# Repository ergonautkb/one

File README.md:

# Ergonaut One

*Ergonaut One in Modern Case*

Ergonaut One is an open-source ergonomic wireless split mechanical keyboard designed by Ergonaut Keyboards.

Inspiration for the keyboard was taken from these projects:

* [Corne](https://github.com/foostan/crkbd) by [foostan](https://github.com/foostan)
* [Dao](https://github.com/yumagulovrn/dao-choc-ble) by [yumagulovrn](https://github.com/yumagulovrn)

## Idea

We wanted to create a pretty affordable, nice looking, and, most importantly, very DIY-friendly ergonomic wireless split keyboard with Gateron Low Profile switches.

## Photos

Gallery can be found on [imgur](https://imgur.com/a/sOBBtmQ).

## Features

* Low-profile, which will reduce strain on your beautiful hands;
* Split. You can put the keyboard where it'll be comfortable exactly for you;
* Pretty long battery life. 250mAh battery gives up to a month of usage without charging;
* Wide availability and range of [compatible keycaps](https://ergonautkb.com/docs/switches/gateron-low-profile#keycaps-compatibility);
* Easily replaceable [switches](https://ergonautkb.com/docs/switches/gateron-low-profile#ks-33-v2) thanks to hot-swap sockets;
* Budget-friendly, because:
  * It uses relatively cheap and widely available [Seeed Studio XIAO nRF52840](https://wiki.seeedstudio.com/XIAO_BLE/) as MCU;
  * It uses one PCB design for both halves of the keyboard;
  * Everything except PCB's, components and hardware (screws, nuts) can be 3D printed.
* Beginner-friendly, because:
  * PCB is easy to solder;
  * Cases are easy to print.
* Wireless by design - no unnecessary wires, no unused connectors on the board;
* Free in terms of hardware design. It's licensed under permissive [CERN-OHL-P v2](https://ohwr.org/cern_ohl_p_v2.pdf) license, which means:
  * you are free to manufacture it yourself;
  * you are free to sell your manufactured hardware for profit.

## Build Guide

BOM and Build Guide can be found in [Ergonaut Keyboards Documentation Portal](https://ergonautkb.com/docs/keyboards/ergonaut-one/intro).

## Firmware

Firmware can be found in [one-zmk-config](https://github.com/ergonautkb/one-zmk-config) repository.

## Gerbers

| Front                                            | Back                                                 |
| ------------------------------------------------ | ---------------------------------------------------- |
|  |  |

* [Gerbers for JLCPCB](../../releases/latest/download/pcb-JLCPCB_gerbers.zip)
* [Gerbers for PCBWay](../../releases/latest/download/pcb-PCBWay_gerbers.zip)

## Community projects

### Accessories

* [Frames for Magic Trackpad 2/3 and Laptops](https://www.thingiverse.com/thing:6447743) by [Alex Kh](https://www.thingiverse.com/alehano777/designs)

## Contacts

* Documentation portal: https://ergonautkb.com
* Telegram: https://ergonautkb.t.me
* Telegram (ru): https://ergonautkb_ru.t.me

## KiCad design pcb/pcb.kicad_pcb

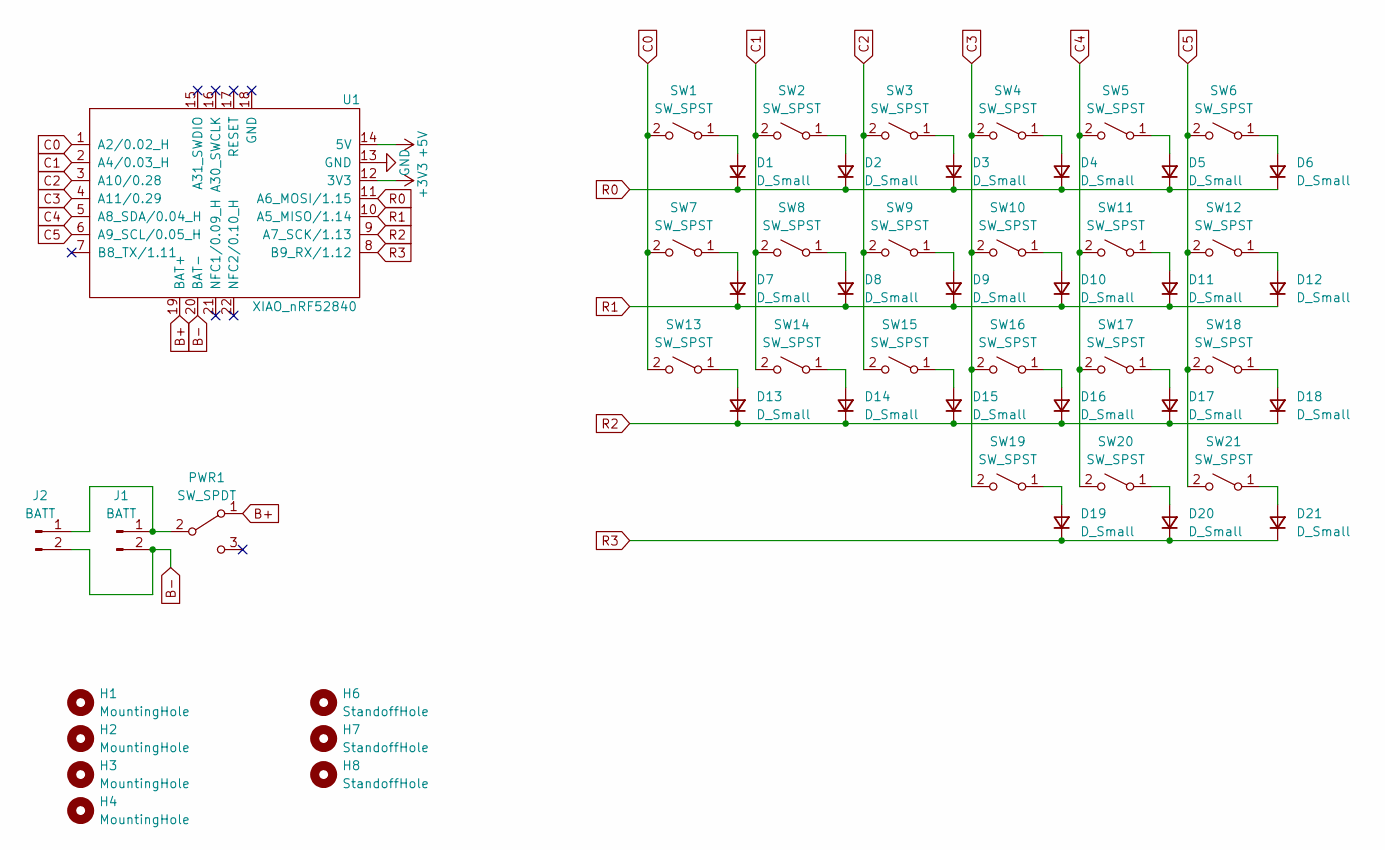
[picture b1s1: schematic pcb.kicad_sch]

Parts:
D1, D2, D3, D4, D5, D6, D7, D8, D9, D10, D11, D12, D13, D14, D15, D16, D17, D18, D19, D20, D21: D_Small; Diode_TH_SMD_DUAL
H1, H2, H3, H4: MountingHole; Hole_4.2mm
H6, H7, H8: StandoffHole; Hole_2.2mm
J1: BATT; Battery
J2: BATT; JST_SH_Battery_DUAL
PWR1: SW_SPDT; MSK-12C02_DUAL
SW1, SW2, SW3, SW4, SW5, SW6, SW7, SW8, SW9, SW10, SW11, SW12, SW13, SW14, SW15, SW16, SW17, SW18, SW19, SW20, SW21: SW_SPST; KS-27_KS-33_Hotswap_1U_DUAL
U1: XIAO_nRF52840; XIAO_nRF52840_DUAL

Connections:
+3V3: U1.12 (3V3)
+5V: U1.14 (5V)
B+: PWR1.1 (A), U1.19 (BAT+)
B-: J1.2, J2.2, U1.20 (BAT-)
C0: SW1.2 (B), SW7.2 (B), SW13.2 (B), U1.1 (A2/0.02_H)
C1: SW2.2 (B), SW8.2 (B), SW14.2 (B), U1.2 (A4/0.03_H)
C2: SW3.2 (B), SW9.2 (B), SW15.2 (B), U1.3 (A10/0.28)
C3: SW4.2 (B), SW10.2 (B), SW16.2 (B), SW19.2 (B), U1.4 (A11/0.29)
C4: SW5.2 (B), SW11.2 (B), SW17.2 (B), SW20.2 (B), U1.5 (A8_SDA/0.04_H)
C5: SW6.2 (B), SW12.2 (B), SW18.2 (B), SW21.2 (B), U1.6 (A9_SCL/0.05_H)
GND: U1.13 (GND)
unnamed: D1.2 (A), SW1.1 (A)
unnamed: D2.2 (A), SW2.1 (A)
unnamed: D3.2 (A), SW3.1 (A)
unnamed: D4.2 (A), SW4.1 (A)
unnamed: D5.2 (A), SW5.1 (A)
unnamed: D6.2 (A), SW6.1 (A)
unnamed: D7.2 (A), SW7.1 (A)
unnamed: D8.2 (A), SW8.1 (A)
unnamed: D9.2 (A), SW9.1 (A)
unnamed: D10.2 (A), SW10.1 (A)
unnamed: D11.2 (A), SW11.1 (A)
unnamed: D12.2 (A), SW12.1 (A)
unnamed: D13.2 (A), SW13.1 (A)
unnamed: D14.2 (A), SW14.1 (A)
unnamed: D15.2 (A), SW15.1 (A)
unnamed: D16.2 (A), SW16.1 (A)
unnamed: D17.2 (A), SW17.1 (A)
unnamed: D18.2 (A), SW18.1 (A)
unnamed: D19.2 (A), SW19.1 (A)
unnamed: D20.2 (A), SW20.1 (A)
unnamed: D21.2 (A), SW21.1 (A)
unnamed: J1.1, J2.1, PWR1.2 (B)
R0: D1.1 (K), D2.1 (K), D3.1 (K), D4.1 (K), D5.1 (K), D6.1 (K), U1.11 (A6_MOSI/1.15)
R1: D7.1 (K), D8.1 (K), D9.1 (K), D10.1 (K), D11.1 (K), D12.1 (K), U1.10 (A5_MISO/1.14)
R2: D13.1 (K), D14.1 (K), D15.1 (K), D16.1 (K), D17.1 (K), D18.1 (K), U1.9 (A7_SCK/1.13)
R3: D19.1 (K), D20.1 (K), D21.1 (K), U1.8 (B9_RX/1.12)

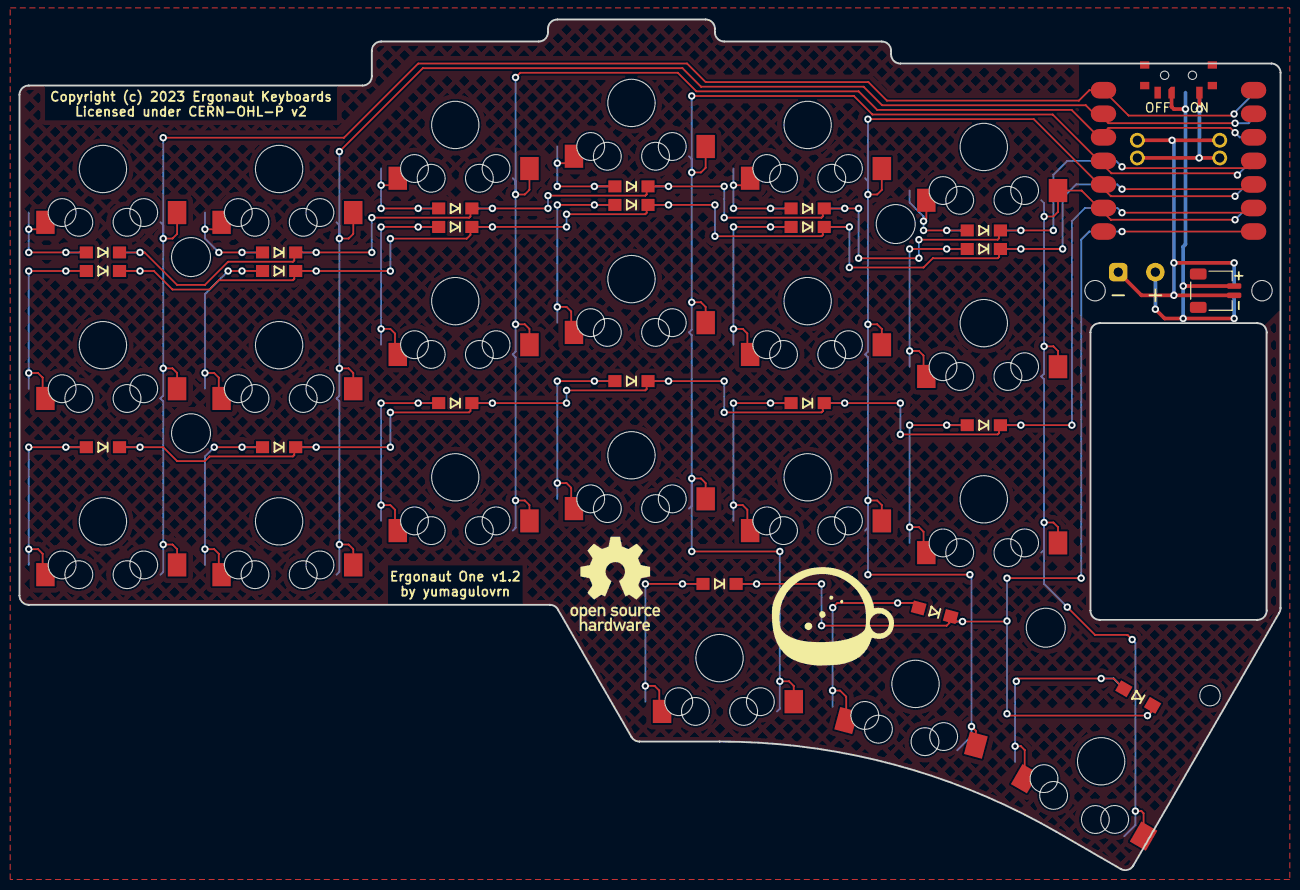
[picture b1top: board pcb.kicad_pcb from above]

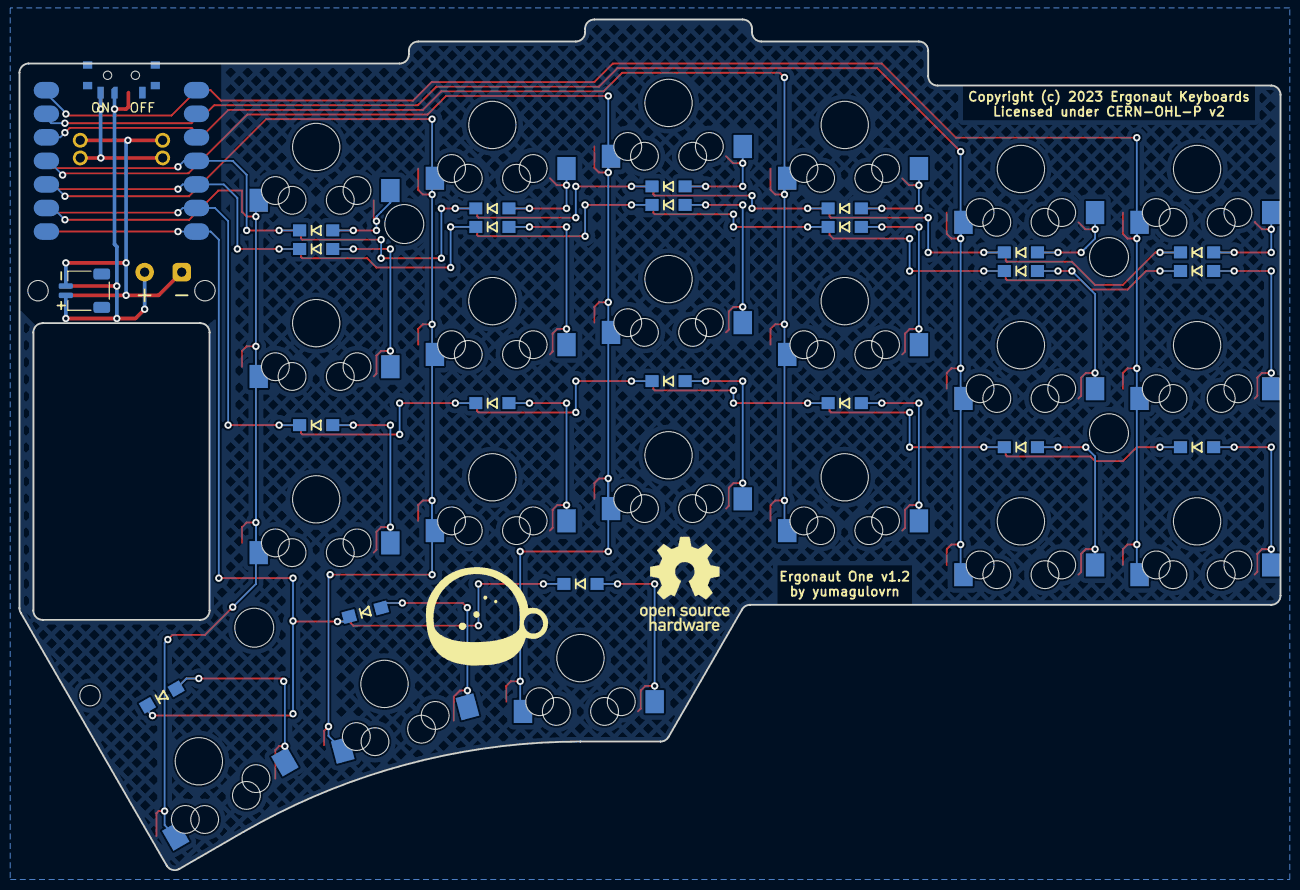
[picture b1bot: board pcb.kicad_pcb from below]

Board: 2 copper layers, 136.0 x 91.7 mm, 53 parts (22 on the bottom side), 34 nets.

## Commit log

2023-06-27 fix plate
2023-07-26 new rev
2023-10-31 preparation for release
2023-10-31 add license
2023-11-02 release 1.1
2023-11-03 naming fixes
2023-11-06 fix cases
2023-11-13 add case fixes
2023-11-13 Production files will be available in Actions
2023-11-13 Build script for automation
2023-11-14 Actions workflow to build production files and images
2023-11-14 Extend actions workflow to upload artifacts
2023-11-14 Add IBOM file for PCB
2023-11-14 Add .gitignore
2023-11-14 Add links to release files to README
2023-11-14 README formatting fix
2023-11-14 fix description
2023-11-14 Revert "Extend actions workflow to upload artifacts"
    This reverts commit de10f4eb546e02318985dd729b3810004abd0f66.
2023-12-07 fix: fix outline fillets
2023-12-10 feat: change fillet radius
2023-12-10 feat: bump board version
2024-01-15 Update README.md
    Added community projects

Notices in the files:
pcb/pcb.kicad_pcb:
Copyright (c) 2023 Ergonaut Keyboards
Licensed under CERN-OHL-P v2
